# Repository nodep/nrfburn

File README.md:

# nrfburn
This is a hardware and software package for flashing Nordic Semiconductors nRF24LE1 and nRF24LU1+ microcontrollers. It consists of three parts: the flasher device with a USB connection, the firmware running on the flasher, and a host program which sends command to the flasher over the USB connection.

### The flasher

The flasher is based around an Atmel AVR ATmega88pa microcontroller running at 12MHz and 3.3V. The PCB is a mixture of through-hole and SMD components chosen as a compromise between size, ease of hand-soldering and mechanical robustness.

It has connectors with pin configurations which allow two popular nRF24LU1+ breakouts and dongles to be directly plugged into the flasher. One is the SparkFun Tranciever Breakout - nRF24LU1+, and the other is the popular nRF USB dongle from ebay.

It also has an 8 pin flat cable connector through which it can flash nRF24LE1 devices as an in-system programmer.

The DBG_LU1 output can be used as a UART debug output from the nRF24LU1+ dongle. There are also two LEDs (DBG1 and DBG2) which can be driven from the SparkFun breakout. This is also useful for debugging.

### The firmware

The flasher firmware communicates with the host PC though [obdev's V-USB](https://www.obdev.at/products/vusb/index.html). It accepts commands from the PC, executes them and sends responses.

### The host PC

The program running on the host PC is a cross-platform (Windows and Linux) command line tool. It does not need special OS drivers because all communication is done through the USB HID class. It's been tested on Windows 7, 8 and 10 and on Linux running on Hardkernel's Odroid X2 board.

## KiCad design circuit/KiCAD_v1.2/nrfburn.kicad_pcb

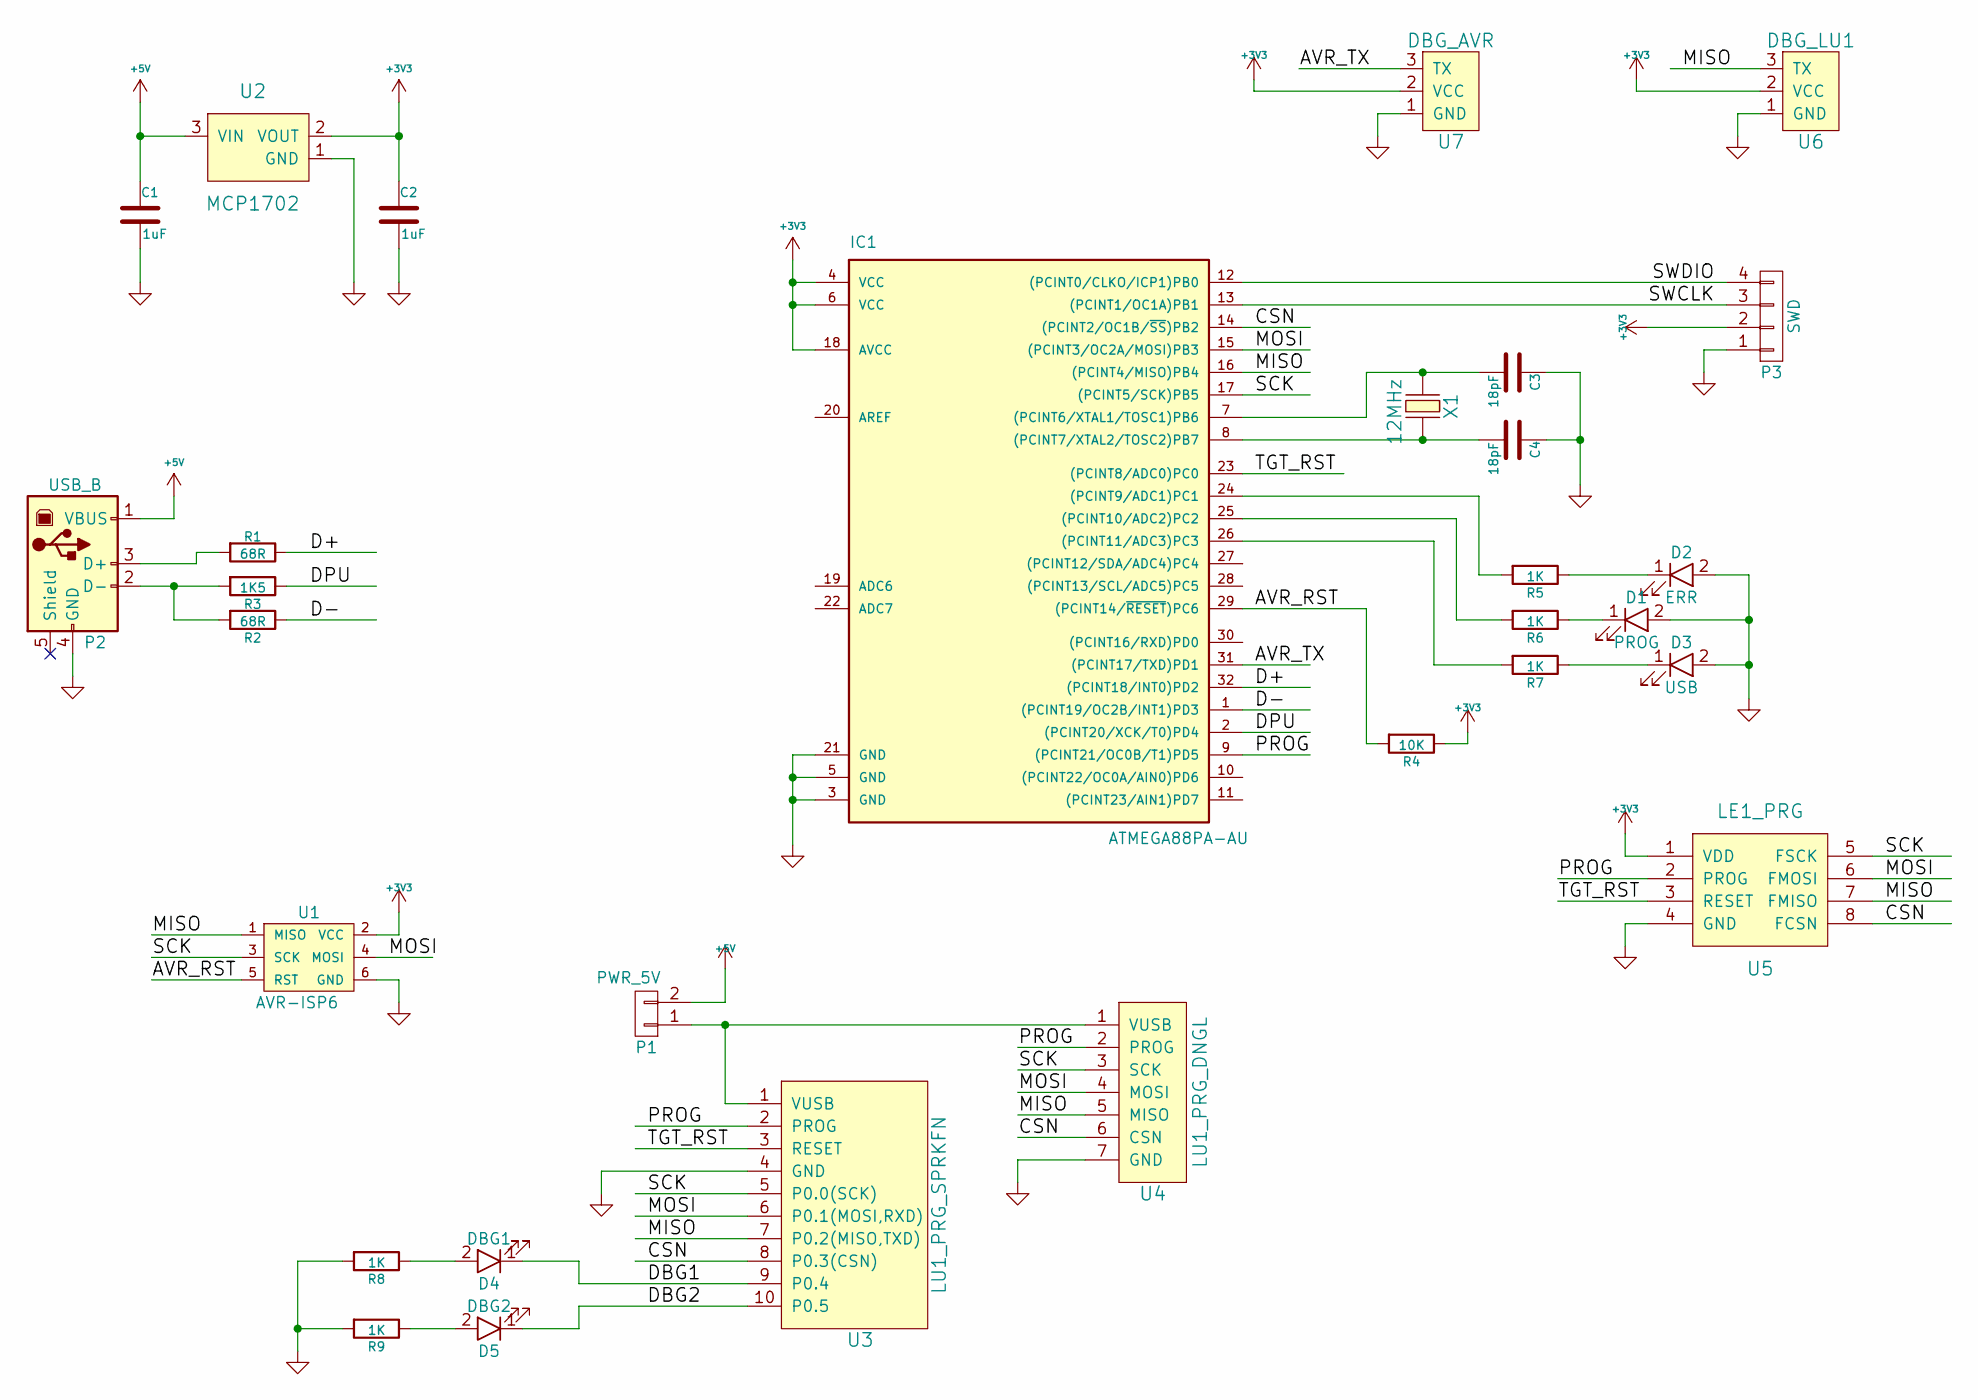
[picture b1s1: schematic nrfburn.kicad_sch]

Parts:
C1, C2: 1uF; c_1206
C3, C4: 18pF; c_1206
D1: PROG; LED-3MM
D2: ERR; LED-3MM
D3: USB; LED-3MM
D4: DBG1; LED-3MM
D5: DBG2; LED-3MM
IC1: ATMEGA88PA-AU; TQFP32
P1: PWR_5V; Pin_Header_Straight_1x02
P2: USB_B; USB_B_loc
P3: SWD; Pin_Header_Straight_1x04
R1, R2: 68R; Resistor_Horizontal_RM10mm
R3: 1K5; Resistor_Horizontal_RM10mm
R4: 10K; Resistor_Horizontal_RM10mm
R5, R6, R7, R8, R9: 1K; Resistor_Horizontal_RM10mm
U1: AVR-ISP6; AVR_ISP6
U2: MCP1702; SOT23
U3: LU1_PRG_SPRKFN; Pin_Header_Straight_1x10
U4: LU1_PRG_DNGL; LU1_PRG_DONGLE
U5: LE1_PRG; NRF_ICSP_RibbonCable
U6: DBG_LU1; Pin_Header_Straight_1x03
U7: DBG_AVR; Pin_Header_Straight_1x03
X1: 12MHz; Crystal_HC49-U_Vertical

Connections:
+3V3: C2.1, IC1.4 (VCC), IC1.6 (VCC), IC1.18 (AVCC), P3.2, R4.1, U1.2 (VCC), U2.2 (VOUT), U5.1 (VDD), U6.2 (VCC), U7.2 (VCC)
+5V: C1.1, P1.2, P2.1 (VBUS), U2.3 (VIN)
/AVR_RST: IC1.29 ((PCINT14/~RESET)PC6), R4.2, U1.5 (RST)
/AVR_TX: IC1.31 ((PCINT17/TXD)PD1), U7.3 (TX)
/CSN: IC1.14 ((PCINT2/OC1B/~SS)PB2), U3.8 (P0.3(CSN)), U4.6 (CSN), U5.8 (FCSN)
/D+: IC1.32 ((PCINT18/INT0)PD2), R1.1
/D-: IC1.1 ((PCINT19/OC2B/INT1)PD3), R2.1
/DBG1: D4.1 (K), U3.9 (P0.4)
/DBG2: D5.1 (K), U3.10 (P0.5)
/DPU: IC1.2 ((PCINT20/XCK/T0)PD4), R3.1
/MISO: IC1.16 ((PCINT4/MISO)PB4), U1.1 (MISO), U3.7 (P0.2(MISO,TXD)), U4.5 (MISO), U5.7 (FMISO), U6.3 (TX)
/MOSI: IC1.15 ((PCINT3/OC2A/MOSI)PB3), U1.4 (MOSI), U3.6 (P0.1(MOSI,RXD)), U4.4 (MOSI), U5.6 (FMOSI)
/PROG: IC1.9 ((PCINT21/OC0B/T1)PD5), U3.2 (PROG), U4.2 (PROG), U5.2 (PROG)
/SCK: IC1.17 ((PCINT5/SCK)PB5), U1.3 (SCK), U3.5 (P0.0(SCK)), U4.3 (SCK), U5.5 (FSCK)
/SWCLK: IC1.13 ((PCINT1/OC1A)PB1), P3.3
/SWDIO: IC1.12 ((PCINT0/CLKO/ICP1)PB0), P3.4
/TGT_RST: IC1.23 ((PCINT8/ADC0)PC0), U3.3 (RESET), U5.3 (RESET)
GND: C1.2, C2.2, C3.1, C4.1, D1.2 (A), D2.2 (A), D3.2 (A), IC1.3 (GND), IC1.5 (GND), IC1.21 (GND), P2.4 (GND), P3.1, R8.2, R9.2, U1.6 (GND), U2.1 (GND), U3.4 (GND), U4.7 (GND), U5.4 (GND), U6.1 (GND), U7.1 (GND)
unnamed: D1.1 (K), R6.1
unnamed: D2.1 (K), R5.1
unnamed: D3.1 (K), R7.1
unnamed: D4.2 (A), R8.1
unnamed: D5.2 (A), R9.1
unnamed: C3.2, IC1.7 ((PCINT6/XTAL1/TOSC1)PB6), X1.1
unnamed: C4.2, IC1.8 ((PCINT7/XTAL2/TOSC2)PB7), X1.2
unnamed: IC1.24 ((PCINT9/ADC1)PC1), R5.2
unnamed: IC1.25 ((PCINT10/ADC2)PC2), R6.2
unnamed: IC1.26 ((PCINT11/ADC3)PC3), R7.2
unnamed: P1.1, U3.1 (VUSB), U4.1 (VUSB)
unnamed: P2.3 (D+), R1.2
unnamed: P2.2 (D-), R2.2, R3.2

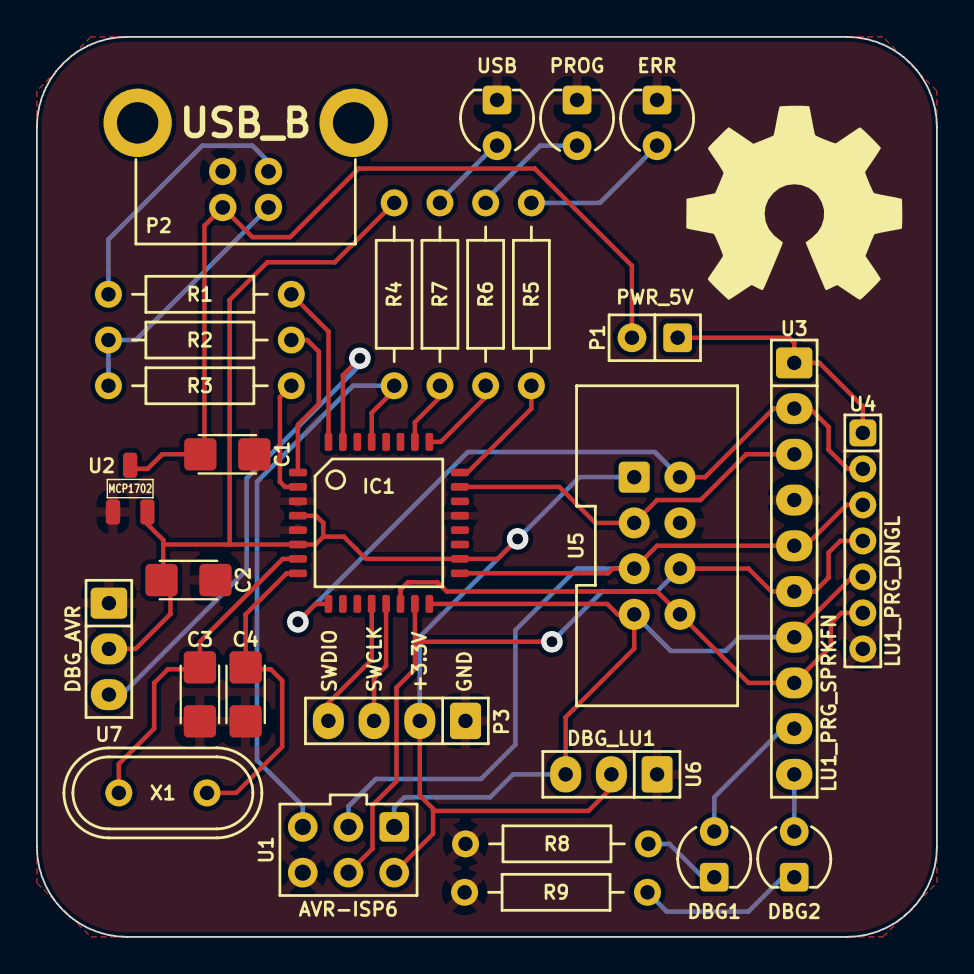
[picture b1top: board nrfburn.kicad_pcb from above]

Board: 2 copper layers, 50.0 x 50.0 mm, 30 parts (0 on the bottom side), 31 nets.

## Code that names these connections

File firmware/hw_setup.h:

#pragma once

// LEDs
#define LED_ERR_PORT	C
#define LED_ERR_BIT		1

#define LED_PROG_PORT	C
#define LED_PROG_BIT	2

#define LED_USB_PORT	C
#define LED_USB_BIT		3


// the nRF24LU1+ and nRF24LE1 programming interface
#define PROG_PORT		D
#define PROG_BIT		5

#define MOSI_PORT		B
#define MOSI_BIT		3

#define CSN_PORT		B
#define CSN_BIT			2

#define SCK_PORT		B
#define SCK_BIT			5

#define MISO_PORT		B
#define MISO_BIT		4

#define TGT_RST_PORT	C
#define TGT_RST_BIT		0


// the nRF51822 SWD interface (not yet implemented)
#define SWDCLK_PORT		B
#define SWDCLK_BIT		5

#define SWDIO_PORT		B
#define SWDIO_BIT		3

#define SWDCLK_HI()		SetBit(PORT(SWDCLK_PORT), SWDCLK_BIT)
#define SWDCLK_LO()		ClrBit(PORT(SWDCLK_PORT), SWDCLK_BIT)

#define SWDIO_HI()		SetBit(PORT(SWDIO_PORT), SWDIO_BIT)
#define SWDIO_LO()		ClrBit(PORT(SWDIO_PORT), SWDIO_BIT)

#define SWDIO_OUT(pu)	SetBit(DDR(SWDIO_PORT), SWDIO_BIT); pu
#define SWDIO_IN(pu)	ClrBit(DDR(SWDIO_PORT), SWDIO_BIT); pu

#define SWDIO_PU_ON		SWDIO_HI
#define SWDIO_PU_OFF	SWDIO_LO

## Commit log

2015-11-03 initial circuit commit
2015-11-03 firmware and software
2016-02-26 Added flasher images
2016-02-26 Testing images
2016-02-26 Add some text to README.md
2016-02-26 File and folder name cleanup
2016-02-26 KiCad schematic and PCB for usable with the new KiCad release (4.0.1)
2016-08-07 added missing files
2016-08-09 debug logging added
2016-11-07 added licence
2020-06-29 replaced auto_ptr<> with vector<>
2025-02-16 moved HW design to KiCad 8
2025-02-16 added 3D models

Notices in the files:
circuit/KiCAD_v1.2/nrfburn.kicad_pcb:
(c) 2025 February 16 Ferenc Szili
